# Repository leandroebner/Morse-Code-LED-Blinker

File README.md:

# Morse Code LED Blinker

> [!WARNING]
> This repository is a work in progress and subject to major changes and updates. The release of the project's source code is currently underway.

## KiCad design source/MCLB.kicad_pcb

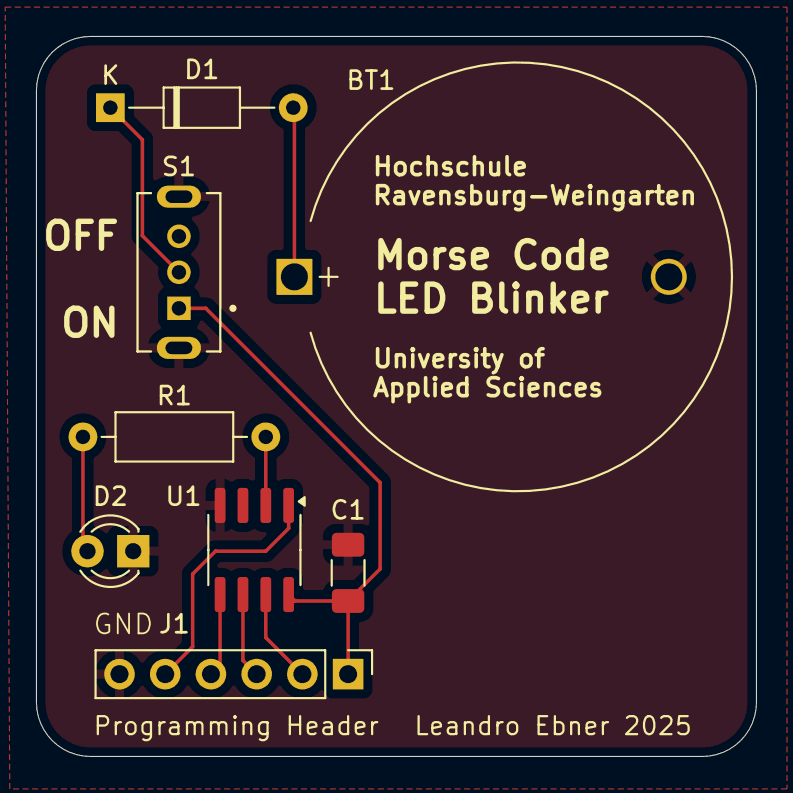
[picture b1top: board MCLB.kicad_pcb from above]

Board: 2 copper layers, 40.0 x 40.0 mm, 8 parts (0 on the bottom side), 10 nets.

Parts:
BT1: CR2032; BatteryHolder_MYOUNG_BS-07-A1BJ001_CR2032
C1: 100nF; C_1206_3216Metric_Pad1.33x1.80mm_HandSolder
D1: 15mA 1V; D_DO-35_SOD27_P10.16mm_Horizontal
D2: 20mA 1.8V-2.4V; LED_D3.0mm
J1: Pinheader 6x 2.54mm; PinHeader_1x06_P2.54mm_Vertical
R1: 390Ω; R_Axial_DIN0207_L6.3mm_D2.5mm_P10.16mm_Horizontal
S1: SPDT; SW_SS12D07VG4
U1: ATtiny13A; SOIC-8_3.9x4.9mm_P1.27mm

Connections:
+BATT: C1.1, J1.1, S1.1, U1.8 (VCC)
GND: BT1.2 (-), C1.2, D2.1 (K), J1.6, S1.S1 (SHIELD), S1.S2 (SHIELD), U1.4 (GND)
MISO: J1.3, U1.6 (PB1)
MOSI: J1.4, U1.5 (PB0)
unnamed: BT1.1 (+), D1.2 (A)
unnamed: D1.1 (K), S1.2
unnamed: D2.2 (A), R1.2
PB3: R1.1, U1.2 (PB3)
SCK: J1.2, U1.7 (PB2)
~RESET: J1.5, U1.1 (~RESET/PB5)

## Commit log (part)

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2025-07-22 Create LICENCE
2025-07-22 Added picture of assembled v1 board
2025-07-28 Create README.md for GH pages
2025-07-29 Create _config.yml for GH pages
2025-07-29 Moved img of v1 board
2025-07-29 Create 404.md for GH pages
2025-07-29 Changed remote theme to supported jekyll theme
2025-07-29 Added custom layout html
2025-07-29 Create style.scss for GH pages
2025-07-29 Update style.scss with RWU colors
2025-07-29 Fixed style.scss order for sass variables
2025-07-29 Update style.scss with headings color
2025-07-29 Update README.md for GH pages
2025-07-29 Changed readme_index plugin flags
2025-07-29 Update liquid if statement in default.html to respect page.show_downloads front matter
2025-07-29 Create home.html to be used as layout for index page
2025-07-29 Moved img of v1 board into assets dir
2025-07-29 Fixed relative img file path in README.md for GH pages
2025-07-29 Update default.html and home.html to have the "improve" link available
2025-07-29 Update _config.yml to display licence in description
2025-07-29 Update _config.yml since no md support in description available
2025-07-29 Update _config.yml to see spacing with different wording
2025-07-29 Fixed spelling typo in _config.yml
2025-07-29 Revert README.md since clickable image wasn't processed by jekyll
2025-08-10 Update README.md since uC model was named wrong
2025-08-10 Create main.cpp in firmware dir
2025-08-10 Update home.html to add navigation buttons
2025-08-10 Update home.html with doc button
2025-08-10 Update README.md to change heading sizes
2025-08-10 Removed site.show_downloads if statement in home.html
2025-08-10 Update 404.html with home button
2025-08-10 Update 404.html with fixed button path
2025-08-10 Update 404.md with different wording
2025-08-10 Update main.cpp with correct LED pin
2025-08-10 Update documentation.md with cpp code
2025-08-10 Update home.html with doc path for button
2025-09-30 Cleaned up code snippet
2025-09-30 Adjusted code snippet in doc
2025-09-30 Update documentation for Arduino Hardware Package
    Added documentation for Arduino Hardware Package and usage.
2025-09-30 Added installation reference for hardware lib
    Added a link to installation documentation for clarity.
2025-10-01 Redid Morse Code implementation and comments
2025-10-01 Improve comments in main.cpp for Morse Code firmware
    Updated comments for clarity and consistency in Morse Code LED Blinker firmware.
2025-10-01 Add warning for syncing main.cpp with Gist ID
    Added a warning about syncing the main.cpp file with a specific Gist ID.
2025-10-01 Replace Arduino code block with gist link
    Updated documentation to include a gist link for Arduino code.
2025-10-02 Rename LICENCE to LICENSE - lol
2025-10-06 Modify download link visibility and footer content
    Updated condition for showing download links and removed footer credits.
2025-10-06 Update project name and footer visibility in home layout
2025-10-06 Change download visibility condition in home layout
2025-10-06 Enhance README with website button and warning
    Added a website button and updated project status warning.
2025-10-06 Remove WHY2025 workshop details from README
    Removed section about the WHY2025 workshop and contact information.
2025-10-06 Restored old 404 layout
2025-10-06 Update 404 page settings
    Remove permalink from 404 page configuration
2025-10-07 Add description field to README front matter
2025-10-13 Update README description to 'Test'
2025-10-13 Change project name and tagline rendering in home layout
2025-10-13 Create CNAME
2025-10-13 Update README description from 'Test' to 'Landing page'
2025-10-13 Create README.md in source directory
2025-10-13 Add KiCad badge to README
2025-10-13 Add 'Take me Home!' link to 404 page
2025-10-13 Simplify 404 page layout by removing links
    Removed GitHub project links and download buttons from 404 page.
2025-10-13 Enhance 404 page with user-friendly message
    Added a 404 error page with a message for users.
2025-10-13 Add assembly documentation
2025-10-13 Testing interactive BOM in assembly documentation - might break jekyll
    Added an interactive BOM iframe and styling to the assembly documentation.
2025-10-15 Change iframe source and some sytling tests
    Updated the iframe source and removed related styles and links.
2025-10-15 Minimal iframe test
2025-10-15 Update assembly.md for interactive BOM display
2025-10-15 Update iframe style for BOM display
2025-10-15 Fix iframe style syntax in assembly.md
2025-10-15 FIXED 404 page relative URL for home button - 100th commit yai
2025-10-15 Added kicad source directory
2025-10-21 Revise documentation description for clarity
    Updated the description to provide clearer information.
2025-10-21 Add Home link to default layout
2025-10-22 Revise documentation for Morse Code LED Blinker setup
    Updated documentation to provide clearer setup instructions for the Morse Code LED Blinker and corrected some formatting issues.
2025-10-22 Update documentation with MicroCore installation steps
    Added instructions for installing the MicroCore package.
2025-10-22 Add programming settings for Morse Code LED Blinker
    Added programming settings section with configuration options for flashing the Morse Code LED Blinker.
2025-10-22 Revise README.md for GH pages for improved project overview
    Updated project description for clarity and detail.
2025-10-22 Add mockup image to project README for GH pages
    Add a mockup image to the README for better visualization.
2025-10-22 Add mockup with lightmode and transparency
2025-10-24 Add hardware revisions and changelog to README
    Added hardware revisions section with changelog.
2025-10-24 Revision table didn't get rendered. Fix with spaces
2025-10-24 Fix typo in hardware revision changelog
2025-10-29 Add GitHub License badge to README
2026-01-21 Add manifest and favicon
2026-01-21 Revise 404 error page content and formatting
    Update 404 page title and add compass emoji.
2026-01-21 Add compass emoji to 404 error message
    Updated the 404 error message to include a compass emoji.
2026-01-21 Enhance documentation with Hardware Assembly section
    Added a section on Hardware Assembly and improved formatting for clarity.
2026-01-24 Fix image syntax for v2 mockup in README
    Updated image syntax in README for v2 mockup.
